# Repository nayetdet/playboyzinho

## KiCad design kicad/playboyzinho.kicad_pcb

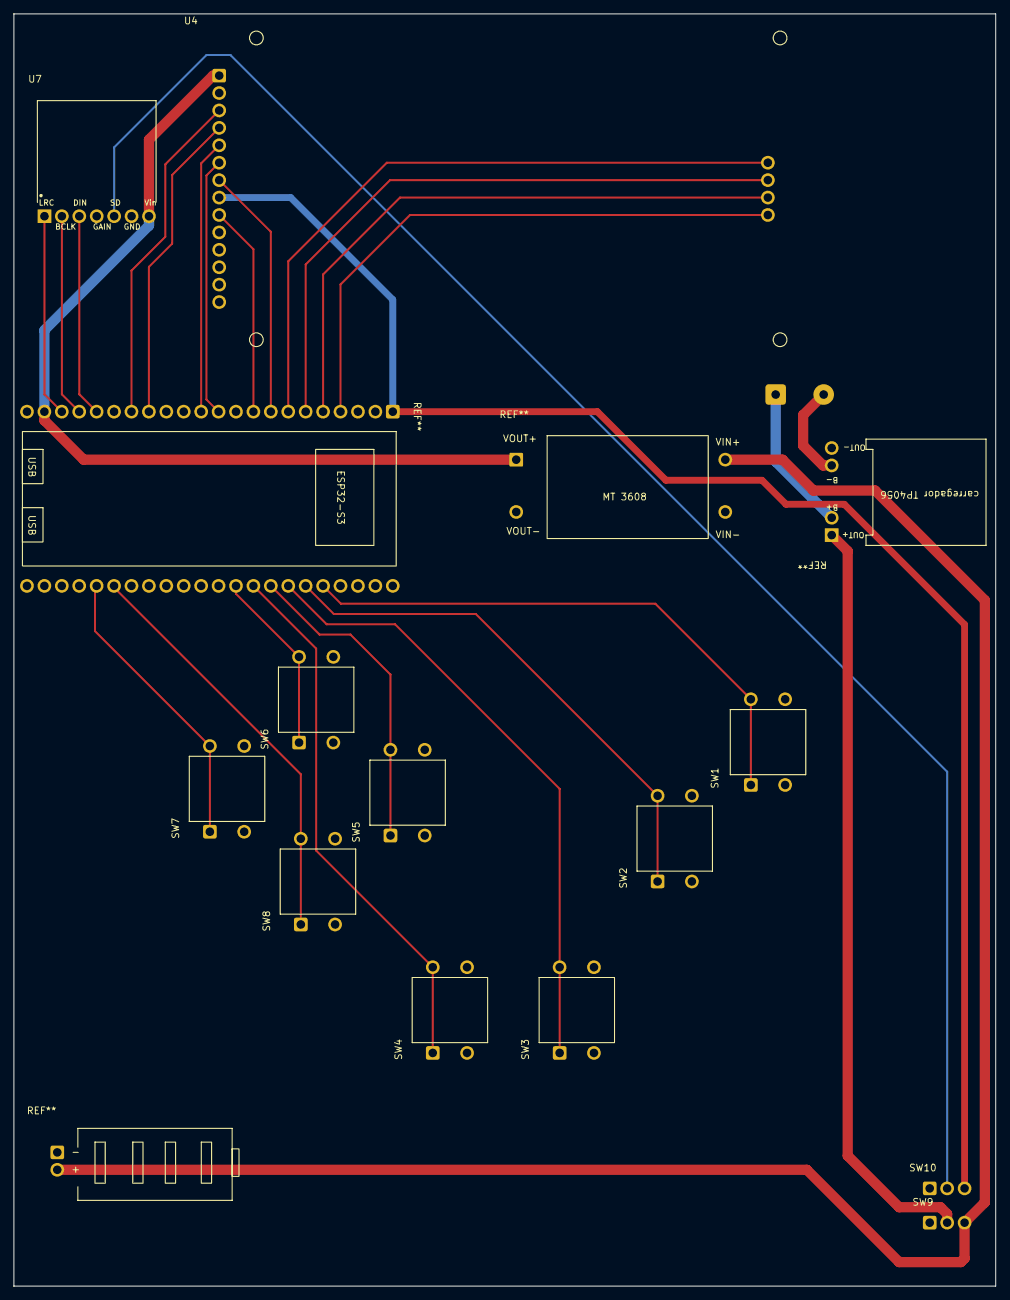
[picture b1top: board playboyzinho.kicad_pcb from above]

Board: 2 copper layers, 143.2 x 185.5 mm, 17 parts (1 on the bottom side), 29 nets.

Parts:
SW1, SW2, SW3, SW4, SW5, SW6, SW7, SW8: SW_Push; botao
SW9, SW10: SW_SPDT; alavanca
U1: esp32-s3-pl; esp32-s3
U2: bateria
U3: (dc dc) MT3608
U4: tela TFT 2.8
U5: (carregador) TP4056
U6: indicador-bateria
U7: (amplificador)_MAX98357_Module; (amplificador) MAX98357_Module

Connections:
+5V: U1.21 (5V), U3.1 (VOUT+), U4.1 (VCC), U7.7 (VIN)
+BATT: U2.1 (BAT+), U5.2 (B+)
-BATT: U2.2 (BAT-), U5.3 (B-)
/3V3: SW10.3 (C), U1.1 (3V3), U4.8 (LED)
/AMP_SD: SW10.2 (B), U7.5 (SD)
/BCLK: U1.19 (GPIO13), U7.2 (BCLK)
/Button-1: SW1.1, U1.27 (GPIO2)
/Button-2: SW2.1, U1.28 (GPIO42)
/Button-3: SW3.1, U1.29 (GPIO41)
/Button-4: SW4.1, U1.31 (GPIO39)
/Button-5: SW5.1, U1.30 (GPIO40)
/Button-6: SW6.1, U1.32 (GPIO38)
/Button-7: SW7.1, U1.40 (GPIO21)
/Button-8: SW8.1, U1.39 (GPIO47)
/DIN: U1.18 (GPIO12), U7.3 (DIN)
/LRC: U1.20 (GPIO14), U7.1 (LRC)
/SD_CS: U1.7 (GPIO7), U4.15 (SD_CS)
/SD_MISO: U1.5 (GPIO5), U4.17 (SD_MISO)
/SD_MOSI: U1.6 (GPIO6), U4.16 (SD_MOSI)
/SD_SCK: U1.4 (GPIO4), U4.18 (SD_SCK)
/TFT_CS: U1.16 (GPIO10), U4.3 (CS)
/TFT_DC: U1.12 (GPIO8), U4.5 (DC)
/TFT_MISO: U1.9 (GPIO16), U4.9 (SDO-(MISO))
/TFT_MOSI: U1.11 (GPIO18), U4.6 (SDI-(MOSI))
/TFT_RESET: U1.15 (GPIO9), U4.4 (RESET)
/TFT_SCK: U1.8 (GPIO15), U4.7 (SCK)
GND: SW1.2, SW2.2, SW3.2, SW4.2, SW5.2, SW6.2, SW7.2, SW8.2, SW10.1 (A), U1.22 (GND), U1.23 (GND), U1.43 (GND), U1.44 (GND), U3.2 (VOUT-), U3.4 (VIN-), U4.2 (GND), U5.4 (OUT-), U6.1 (BAT-), U7.6 (GND)
unnamed: SW9.2 (B), U5.1 (OUT+)
unnamed: SW9.3 (C), U3.3 (VIN+), U6.2 (BAT+)

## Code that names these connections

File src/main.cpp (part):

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#include <Adafruit_ILI9341.h>

// TFT ILI9341
#define TFT_CS 10
#define TFT_DC 8
#define TFT_RST 9
#define TFT_MOSI 18
#define TFT_SCK 15
#define TFT_MISO 16

// SW1 a SW8: pressionar conecta a entrada ao GND (ativo em LOW).
constexpr uint8_t BUTTON_PINS[] = {2, 42, 41, 39, 40, 38, 21, 47};
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#include <freertos/queue.h>

// Cartao SD em um controlador SPI independente da tela.
#define SD_CS 7
#define SD_MOSI 6
#define SD_MISO 5
#define SD_SCK 4

// MAX98357A
#define I2S_BCLK 13
#define I2S_LRC 14
#define I2S_DIN 12
#define AMP_SD 11

// Arquivo rawvideo gerado pelo FFmpeg: RGB565 little-endian, 320x240, 10 FPS.
constexpr char VIDEO_PATH[] = "/video.rgb565";
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}

bool initDisplayAndSd() {
  pinMode(SD_CS, OUTPUT);
  digitalWrite(SD_CS, HIGH);

  tftSpi.begin(TFT_SCK, TFT_MISO, TFT_MOSI, TFT_CS);
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}

void setup() {
  pinMode(AMP_SD, OUTPUT);
  digitalWrite(AMP_SD, LOW);
  for (uint8_t pin : BUTTON_PINS) {
    pinMode(pin, INPUT_PULLUP);
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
